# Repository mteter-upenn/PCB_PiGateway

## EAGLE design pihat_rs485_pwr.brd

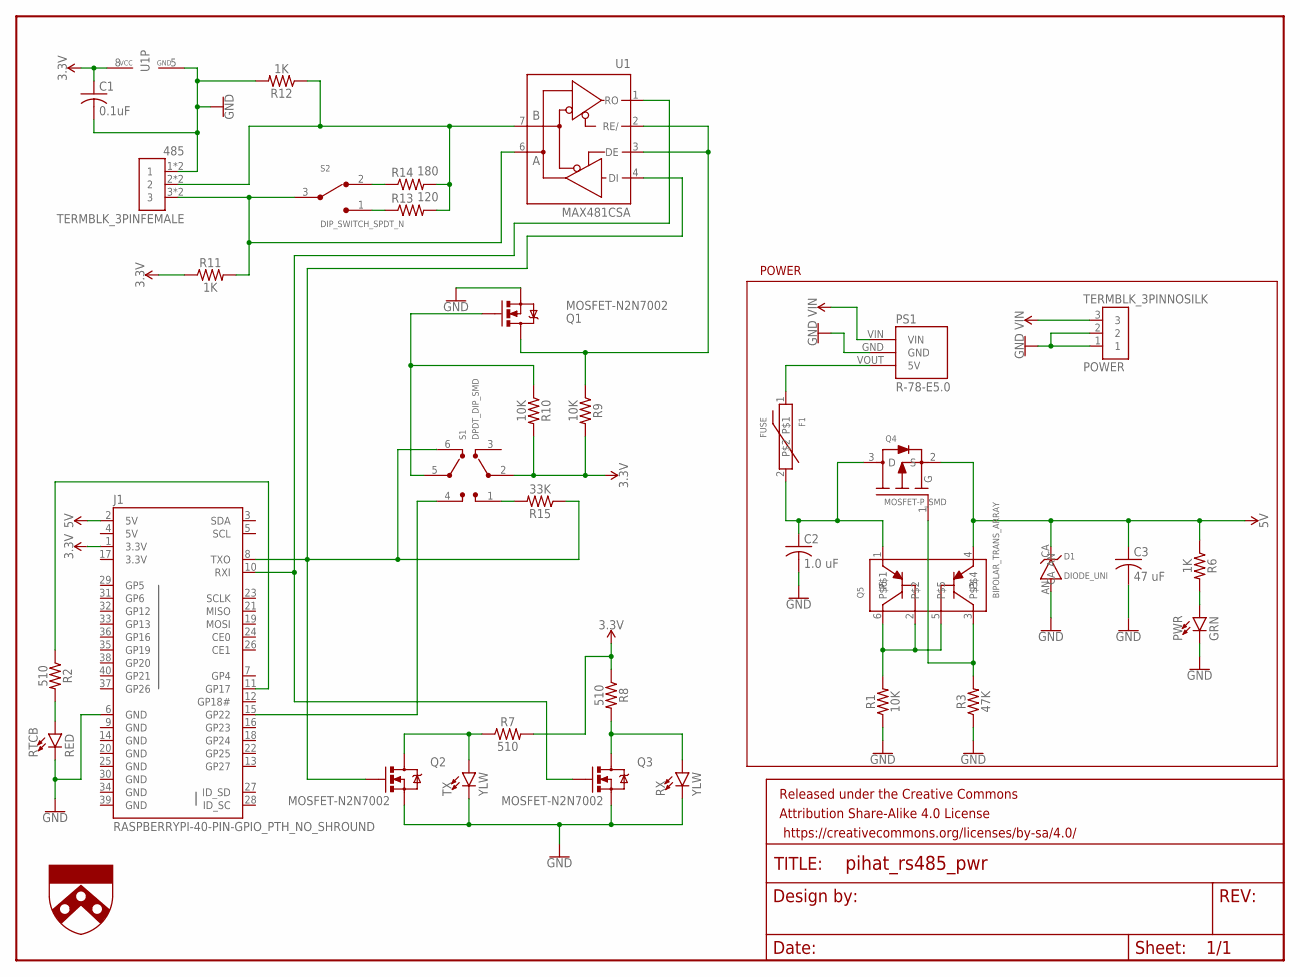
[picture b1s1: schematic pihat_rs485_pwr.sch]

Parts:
485: TERMBLK_3PINFEMALE; TERMBLK_FEMALE_3PIN_90_NOSILK
C1: 0.1uF; C0603
C2: 1.0 uF; C0603
C3: 47 uF; C0603
D1: DIODE_UNI; DO-214AA_UNI
F1: FUSE; 1812_STD_BI
FRAME1: FRAME-LETTERNO_PACKAGE; DUMMY
J1: RASPBERRYPI-40-PIN-GPIO_PTH_NO_SHROUND; PI_2X20
POWER: TERMBLK_3PINNOSILK; TERMBLK_3PIN_90_NOSILK
PS1: R-78-E5.0; R-78-EXX
PWR: GRN; LED-0603
Q1, Q2, Q3: MOSFET-N2N7002; SOT23-3
Q4: MOSFET-P_SMD; SOT23-3
Q5: BIPOLAR_TRANS_ARRAY; SOT363
R1, R9, R10: 10K; 0603
R2, R7, R8: 510; 0603
R3: 47K; 0603
R6, R11, R12: 1K; 0603
R13: 120; 0603
R14: 180; 0603
R15: 33K; 0603
RTCB: RED; LED-0603
RX: YLW; LED-0603
S1: DPDT_DIP_SMD
S2: DIP_SWITCH_SPDT_N; SINGLE_DIP_SW_NEUT
TX: YLW; LED-0603
U1: MAX481CSA; SO08
U$4: UPENN_SHIELD_.3_SILK; UPENN_SHIELD_3_SILK

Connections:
3.3V: C1.1, J1.1 (3.3V), J1.17 (3.3V), R7.2, R8.1, R9.2, R10.2, R11.1, S1.2 (<2), U1.8 (VCC)
5V: C3.1, D1.CA, J1.2 (5V), J1.4 (5V), Q4.2 (S), Q5.4, R6.1
GND: 485.1, 485.4 (1), C1.2, C2.2, C3.2, D1.AN, J1.6 (GND), J1.9 (GND), J1.14 (GND), J1.20 (GND), J1.25 (GND), J1.30 (GND), J1.34 (GND), J1.39 (GND), POWER.1, POWER.2, PS1.GND, PWR.C, Q1.2 (S), Q2.2 (S), Q3.2 (S), R1.1, R3.1, R12.2, RTCB.C, RX.C, TX.C, U1.5 (GND)
unnamed: R14.1, S2.2
unnamed: J1.15 (GP22), S1.4 (4>)
unnamed: J1.8 (TXO), Q2.1 (G), R15.1, S1.6 (6>), U1.4 (DI)
unnamed: Q5.2, Q5.5, Q5.6, R1.2
unnamed: Q4.1 (G), Q5.3, R3.2
unnamed: C2.1, F1.2, Q4.3 (D), Q5.1
unnamed: F1.1, PS1.VOUT (5V)
unnamed: R13.1, S2.1
unnamed: 485.2, 485.5 (2), R12.1, R13.2, R14.2, U1.7 (B)
unnamed: PWR.A, R6.2
unnamed: R15.2, S1.1 (<1)
unnamed: J1.10 (RXI), Q3.1 (G), U1.1 (RO)
unnamed: R2.2, RTCB.A
unnamed: J1.11 (GP17), R2.1
unnamed: 485.3, 485.6 (3), R11.2, S2.3, U1.6 (A)
unnamed: Q1.1 (G), R10.1, S1.5 (5>)
unnamed: Q1.3 (D), R9.1, U1.2 (RE/), U1.3 (DE)
unnamed: Q3.3 (D), R8.2, RX.A
unnamed: Q2.3 (D), R7.1, TX.A
VIN: POWER.3, PS1.VIN

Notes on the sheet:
POWER

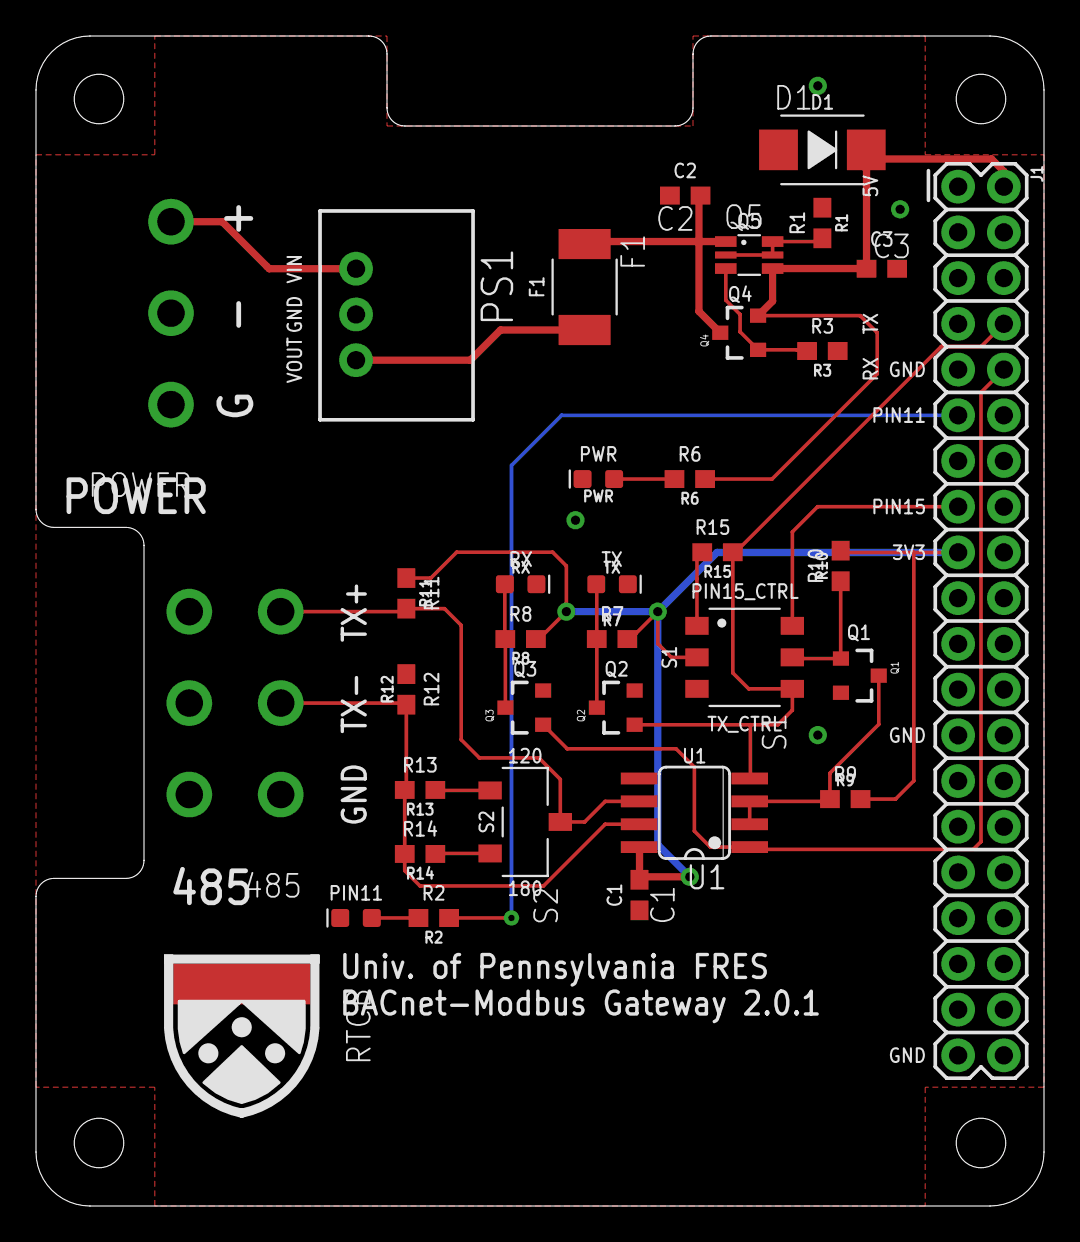
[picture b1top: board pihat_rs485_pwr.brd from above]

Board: 2 copper layers, 56.0 x 65.0 mm, 36 parts (0 on the bottom side), 23 nets.

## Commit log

2017-10-09 10/9/17, first commit with files
2017-10-09 10/9/17, removed teensy, changed board dims
2017-10-16 10/16/17, mostly set
2017-10-16 10/16/17, all silkscreens placed
2017-10-16 10/16/17, made gerber files
2017-10-16 10/16/17, adjusted r14 to 180ohms
2017-10-20 10/20/17, schrunk board size
2017-11-29 11/29/17, added text file to delineate board designs
2017-11-29 11/29/17, changed PS, term blocks
2017-11-30 11/30/17, changes to silkscreen
2017-11-30 11/30/17, moved some parts, updated gerbers
2018-01-04 1/4/18, moved D1 and C3, updated gerbers
2018-01-08 1/8/18, change R2 value from 680 to 510 to reduce parts
2018-01-08 1/8/18, updated purchase list
2018-02-01 2/1/18, minor silkscreen changes
2018-02-01 2/1/18, update gerbers
2018-02-01 2/1/18, update purchase list stocks

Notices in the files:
parts and their libraries:
SparkFun-Aesthetics: Licensing: Creative Commons ShareAlike 4.0 International - https://creativecommons.org/licenses/by-sa/4.0
SparkFun-Aesthetics: Released under the Creative Commons Attribution Share-Alike 4.0 License
SparkFun-Aesthetics: https://creativecommons.org/licenses/by-sa/4.0
